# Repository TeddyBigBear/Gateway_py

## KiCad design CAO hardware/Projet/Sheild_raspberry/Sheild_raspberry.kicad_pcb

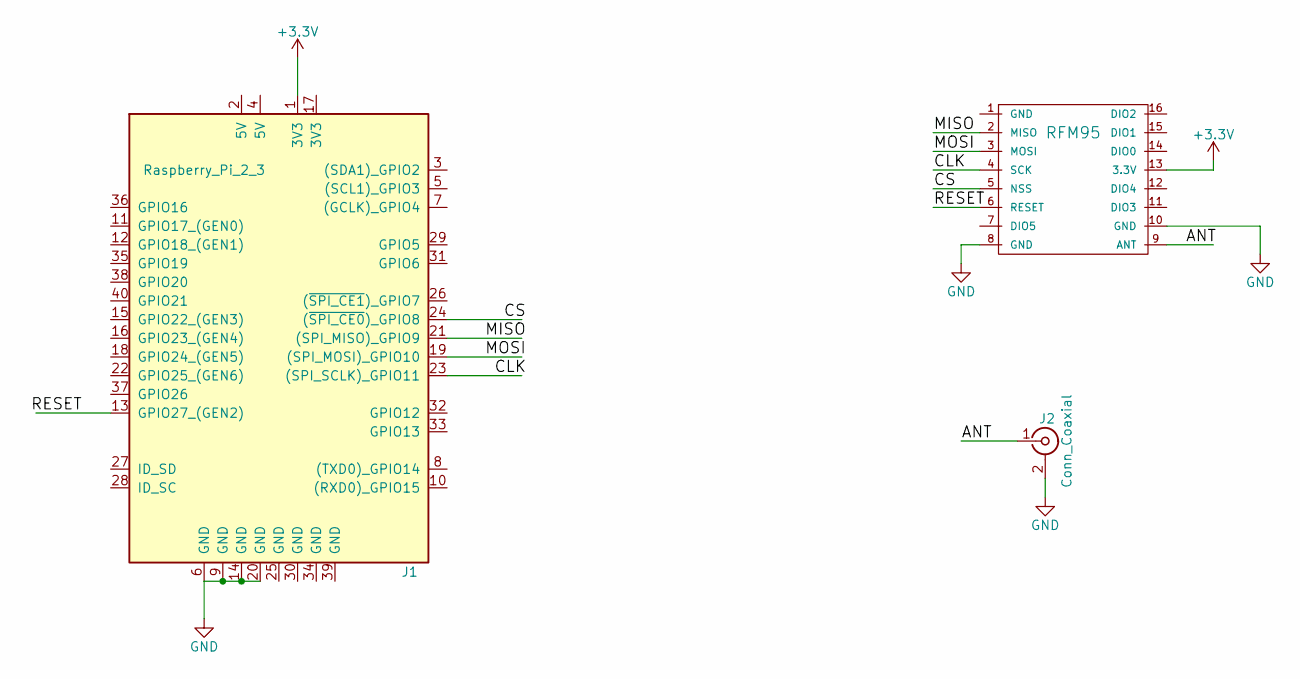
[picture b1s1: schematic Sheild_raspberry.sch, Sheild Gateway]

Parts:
J1: Raspberry_Pi_2_3; Pin_Header_Angled_2x20_Pitch2.54mm
J2: Conn_Coaxial; Molex_SMA_Jack_Edge_Mount
LoRa1: RFM95; Hopref_RFM9XW_SMD

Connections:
+3V3: J1.1 (3V3), LoRa1.13 (3.3V)
/ANT: J2.1 (In), LoRa1.9 (ANT)
/CLK: J1.23 ((SPI_SCLK)_GPIO11), LoRa1.4 (SCK)
/CS: J1.24 ((~SPI_CE0~)_GPIO8), LoRa1.5 (NSS)
/MISO: J1.21 ((SPI_MISO)_GPIO9), LoRa1.2 (MISO)
/MOSI: J1.19 ((SPI_MOSI)_GPIO10), LoRa1.3 (MOSI)
/RESET: J1.13 (GPIO27_(GEN2)), LoRa1.6 (RESET)
GND: J1.6 (GND), J1.9 (GND), J1.14 (GND), J1.20 (GND), J2.2 (Ext), LoRa1.8 (GND), LoRa1.10 (GND)

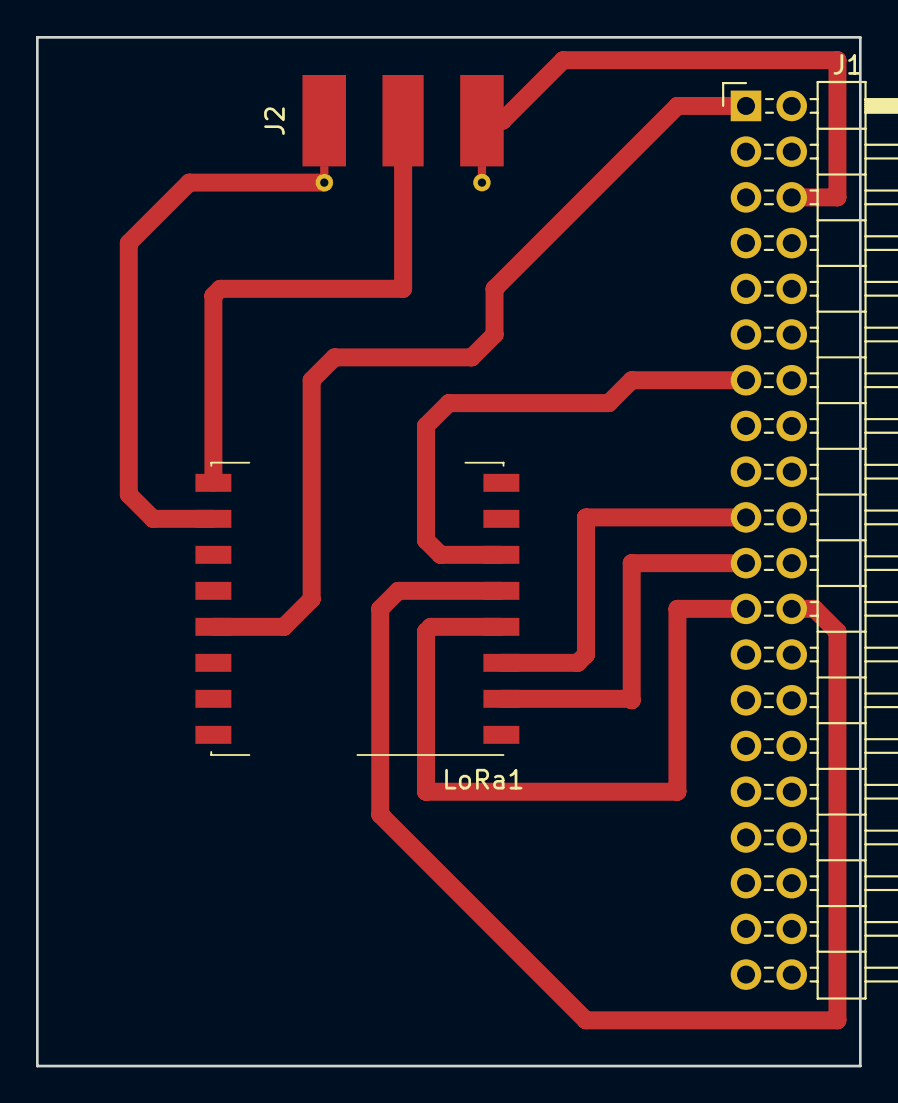
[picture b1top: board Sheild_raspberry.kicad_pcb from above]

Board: 2 copper layers, 45.7 x 57.2 mm, 3 parts (0 on the bottom side), 8 nets.

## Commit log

2017-11-09 added txt file
2017-11-09 Modif 1
2017-11-09 Script for files
    created two files to manage the text file we use as buffer
2017-11-16 Ajout Fichier word pour le rapport
    la synchro est delicate alors il vaut mieux ne pas le modifier en meme temps
2017-11-16 reorganisation en sous fichier
2017-11-16 changer nom fichier
2017-12-17 Ajout du fichier des taches et d'un powerpoint explicatif pour github
    Le fichier Exel et le powerpoint sont a la racine et j'ai mis une sauvegarde des notes de google docs dans Rapport et annexes
2017-12-17 Répartition des taches avec Xmind
    Je teste le logiciel Xmind pour répartir les taches, le trouve pas mal. Voici le lien si vous voulez le tester :
    https://www.xmind.net
    J'ai mis également un fichier où j'ai commencé à répartir les taches.
2018-02-10 Ajout codes Sonia
2018-02-10 Re-organisation
    On a changer l'organisation du dossier GitHub
2018-02-11 Modifs codes et ajout Planning
    Dans le dossier Organisation (dans Gestion Projet) vous pouvez trouver un planning sur les plusieurs mois à venir pour s'organiser
2018-02-22 MAJ Code et ajout doc trame
2018-02-27 J'ai créé un fichier
    Taille antenne
2018-03-02 Re-organisation dossier + ajout partie HW
    J'ai ajouter la partie HW avec des fichier de CAO et des shema
    Il y a aussi un fichier "Table des matieres" qui contiens une organisation generale du rapport il est a detailler
2018-03-08 Added files for CAO
    I currently have a pcb design almost ready to use
2018-03-09 Mise à jour docs
    MAJ sur les infos de la trame et le sommaire du rapport
2018-03-11 ESP32 software configuration
2018-04-09 Partie Elaboration Shield Raspberry
    à Mettre à jour par la suite
2018-04-12 Ajout photos ruches
    C'est le rucher du prof
2018-04-12 Mise a jour datasheet
2018-04-12 Ajout exemple code RFM
    Full definition des registres
2018-04-12 Mise a jour fichiers CAO
2018-04-16 LoRa
    petite doc LoRa
2018-04-16 Update
    Last lora commit failed
2018-04-23 Modif
2018-05-02 Finalisation du code
